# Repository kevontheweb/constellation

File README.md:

# constellation
Earings that look like a constellation, using an attiny to give it some sparkle ✨

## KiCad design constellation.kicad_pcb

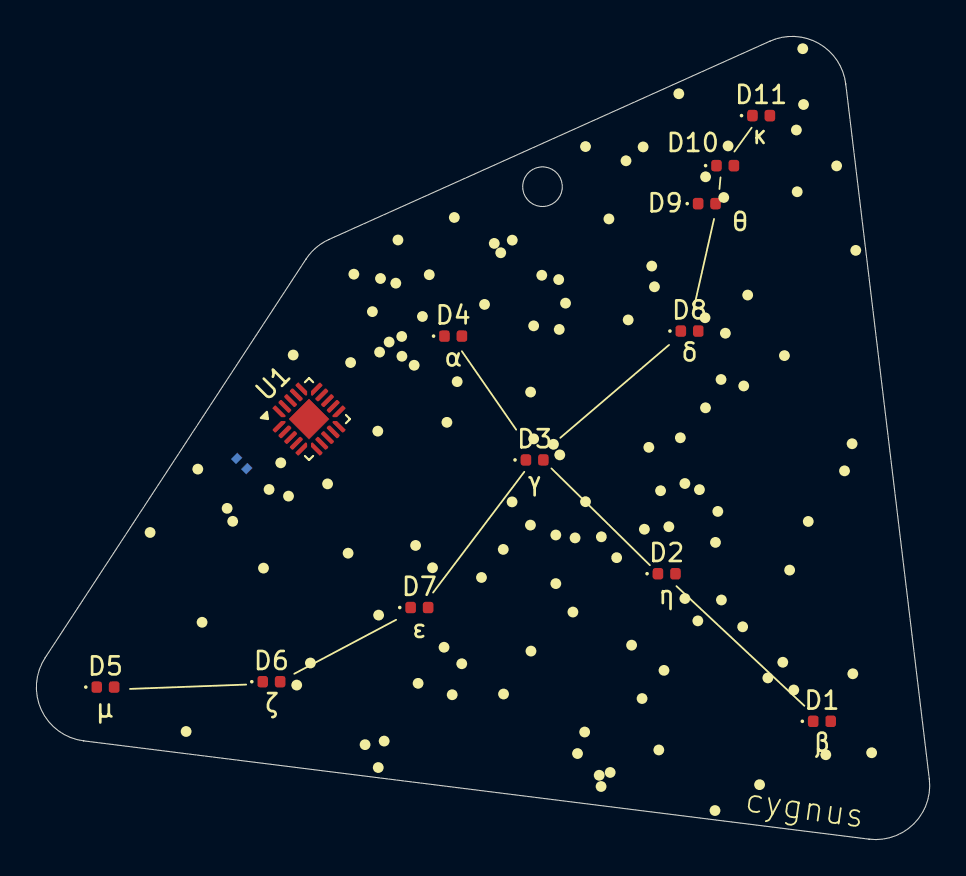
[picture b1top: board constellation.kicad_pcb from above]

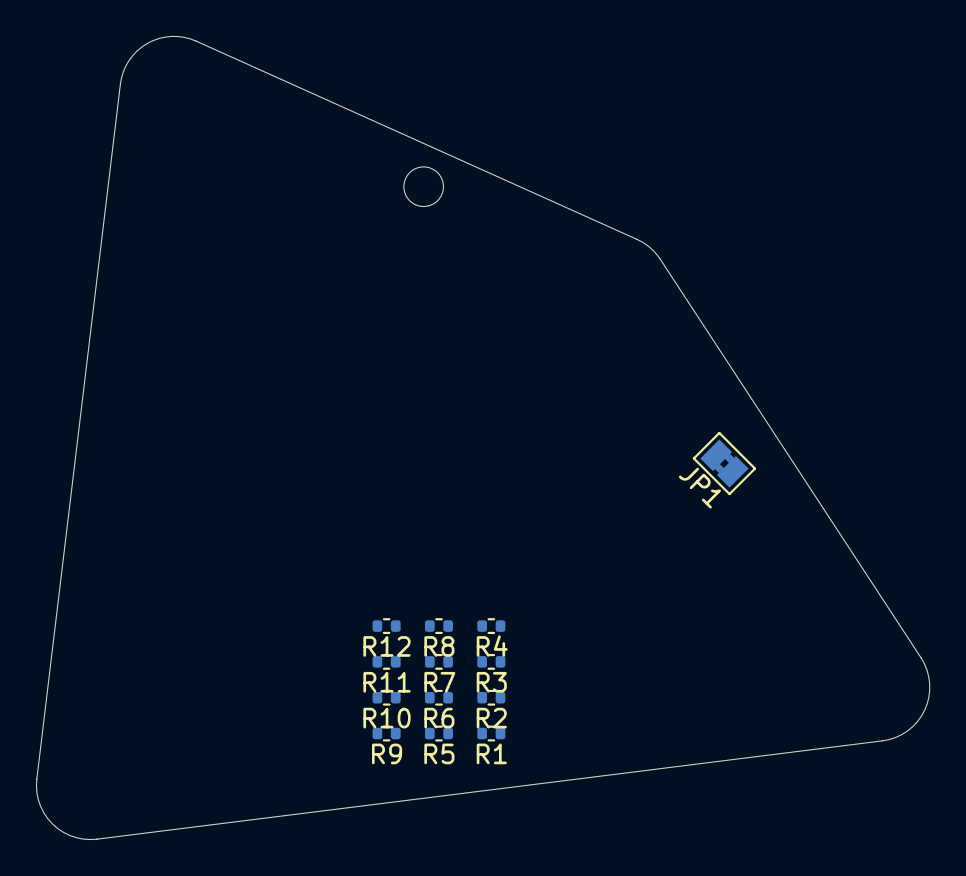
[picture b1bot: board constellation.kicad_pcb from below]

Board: 2 copper layers, 49.6 x 44.6 mm, 27 parts (14 on the bottom side), 24 nets, no tracks yet.

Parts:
BT1: Battery_Cell; Battery_CR1225
D1: β; D_0402_1005Metric
D2: η; D_0402_1005Metric
D3: γ; D_0402_1005Metric
D4: α; D_0402_1005Metric
D5: μ; D_0402_1005Metric
D6: ζ; D_0402_1005Metric
D7: ε; D_0402_1005Metric
D8: δ; D_0402_1005Metric
D9: θ; D_0402_1005Metric
D10: ι; D_0402_1005Metric
D11: κ; D_0402_1005Metric
H1: MountingHole; MountingHole_2.2mm_M2
JP1: SolderJumper_2_Open; SolderJumper-2_P1.3mm_Bridged2Bar_Pad1.0x1.5mm
R1: 100k; R_0402_1005Metric
R2, R3, R4, R5, R6, R7, R8, R9, R10, R11, R12: 0R; R_0402_1005Metric
U1: ATtiny20-MM; QFN-20-1EP_3x3mm_P0.45mm_EP1.6x1.6mm

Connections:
/ALBIREO_β: R9.1, U1.15 (PA7)
/ALJANAH_ε: R4.1, U1.3 (PA2)
/SADR_γ: R11.1, U1.12 (PB1)
/δ: R5.1, U1.2 (PA3)
/ζ: R3.1, U1.4 (PA1)
/η: R10.1, U1.11 (PB0)
/θ: R6.1, U1.1 (PA4)
/ι: R7.1, U1.17 (PA5)
/κ: R8.1, U1.16 (PA6)
/μ: R2.1, U1.5 (PA0)
GND: D1.1 (K), D2.1 (K), D3.1 (K), D4.1 (K), D5.1 (K), D6.1 (K), D7.1 (K), D8.1 (K), D9.1 (K), D10.1 (K), D11.1 (K), JP1.2 (B), U1.8 (GND), U1.21 (GND)
unnamed: D1.2 (A), R9.2
unnamed: D2.2 (A), R10.2
unnamed: D3.2 (A), R11.2
unnamed: D4.2 (A), R12.2
unnamed: D5.2 (A), R2.2
unnamed: D6.2 (A), R3.2
unnamed: D7.2 (A), R4.2
unnamed: D8.2 (A), R5.2
unnamed: D9.2 (A), R6.2
unnamed: D10.2 (A), R7.2
unnamed: D11.2 (A), R8.2
unnamed: JP1.1 (A), R1.2, U1.13 (~RESET/PB3)
VCC: R1.1, U1.9 (VCC)

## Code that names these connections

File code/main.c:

// Code for ATtiny85 (or similar) with flickering and PWM

#include <avr/io.h>
#include <util/delay.h>
#include <stdlib.h>

// Define LED pins (adjust if needed)
#define D1 PB0
#define D2 PB1
#define D3 PB2
#define D4 PB3
#define D5 PB4
#define D6 PA7
#define D7 PA6
#define D8 PA5
#define D9 PA4
#define D10 PA3
#define D11 PA2

// PWM settings
#define PWM_MAX 255 // Maximum PWM value (brightness)

void setup() {
  // Set LED pins as outputs
  DDRB = (1 << D1) | (1 << D2) | (1 << D3) | (1 << D4) | (1 << D5);
  DDRA = (1 << D6) | (1 << D7) | (1 << D8) | (1 << D9) | (1 << D10) | (1 << D11);

  // Initialize PWM (example using Timer0 for PB0, PB1, and Timer1 for the rest. Adjust as needed)
  TCCR0A = (1 << COM0A1) | (1 << COM0B1) | (1 << WGM00) | (1 << WGM01); // Fast PWM mode
  TCCR0B = (1 << CS01); // Prescaler 8 (adjust as needed)

  TCCR1A = (1 << COM1A1) | (1 << COM1B1) | (1 << WGM10); // Fast PWM mode
  TCCR1B = (1 << CS11); // Prescaler 8 (adjust as needed)
}

void flickerLED(uint8_t ledPin, uint8_t port, uint8_t timerRegister) {
  uint8_t pwmValue = rand() % PWM_MAX; // Random PWM value
  if (port == 0) {
    if (ledPin == D1) {
      OCR0A = pwmValue;
    } else if (ledPin == D2) {
      OCR0B = pwmValue;
    } else {
      PORTB = (1 << ledPin);
      OCR0A = pwmValue;
    }
  } else {
    if (ledPin == D6) {
      OCR1A = pwmValue;
    } else {
      OCR1B = pwmValue;
    }
    PORTA = (1 << ledPin);
  }
  _delay_ms(rand() % 500); // Random delay
}

void loop() {
  // Flicker LEDs semi-randomly
  flickerLED(D1, 0, 0);
  flickerLED(D2, 0, 0);
  flickerLED(D3, 0, 0);
  flickerLED(D4, 0, 0);
  flickerLED(D5, 0, 0);
  flickerLED(D6, 1, 1);
  flickerLED(D7, 1, 1);
  flickerLED(D8, 1, 1);
  flickerLED(D9, 1, 1);
  flickerLED(D10, 1, 1);
  flickerLED(D11, 1, 1);
}

int main() {
  setup();
  while (1) {
    loop();
  }
  return 0;
}

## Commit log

2025-04-04 🧘🏻 vibe coding
